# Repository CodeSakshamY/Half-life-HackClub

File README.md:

# Half-life-HackClub
# Psycon-wearable-pcb-V1

custom pcb for my psycon wearable project. designed in easyeda.

## THE BOARD

It is an pcb board loaded with various sensors powered with esp32 as its main brain which would basically help me in making my first version of a smart watch like health wearable
## COMPONENTS

- **ESP32-WROOM-32D** — main microcontroller
- **MAX30102** — optical pulse sensor
- **MPU6050** — accelerometer + gyroscope
- **MCP9808** — temperature sensor
- **ADS1115** — 16-bit adc
- **CH340C** — usb-to-serial interface
- **TP4056** — lithium-ion battery charger
- **AP2112K-3.3** — 3.3v voltage regulator
- **ME6211C18** — 1.8v voltage regulator
- **USB-C + micro-usb connectors**
- **JST-PH connector** — battery connection
- resistors, capacitors, switches and usb protection components

## PCB DESIGN

schematic, component placement and routing are done in easyeda.

## IMAGES

### 3d view

### pcb routing

### schematic

designing is done. next step is getting the board manufactured, recieving it , adding the code and testing it and seeing if everything works!!

The entire pcb was designed in easyeda but duet to the repo submision checks error i have added the .kicad_pcb file but please refer to only the files in the folder named psycon-wearable.

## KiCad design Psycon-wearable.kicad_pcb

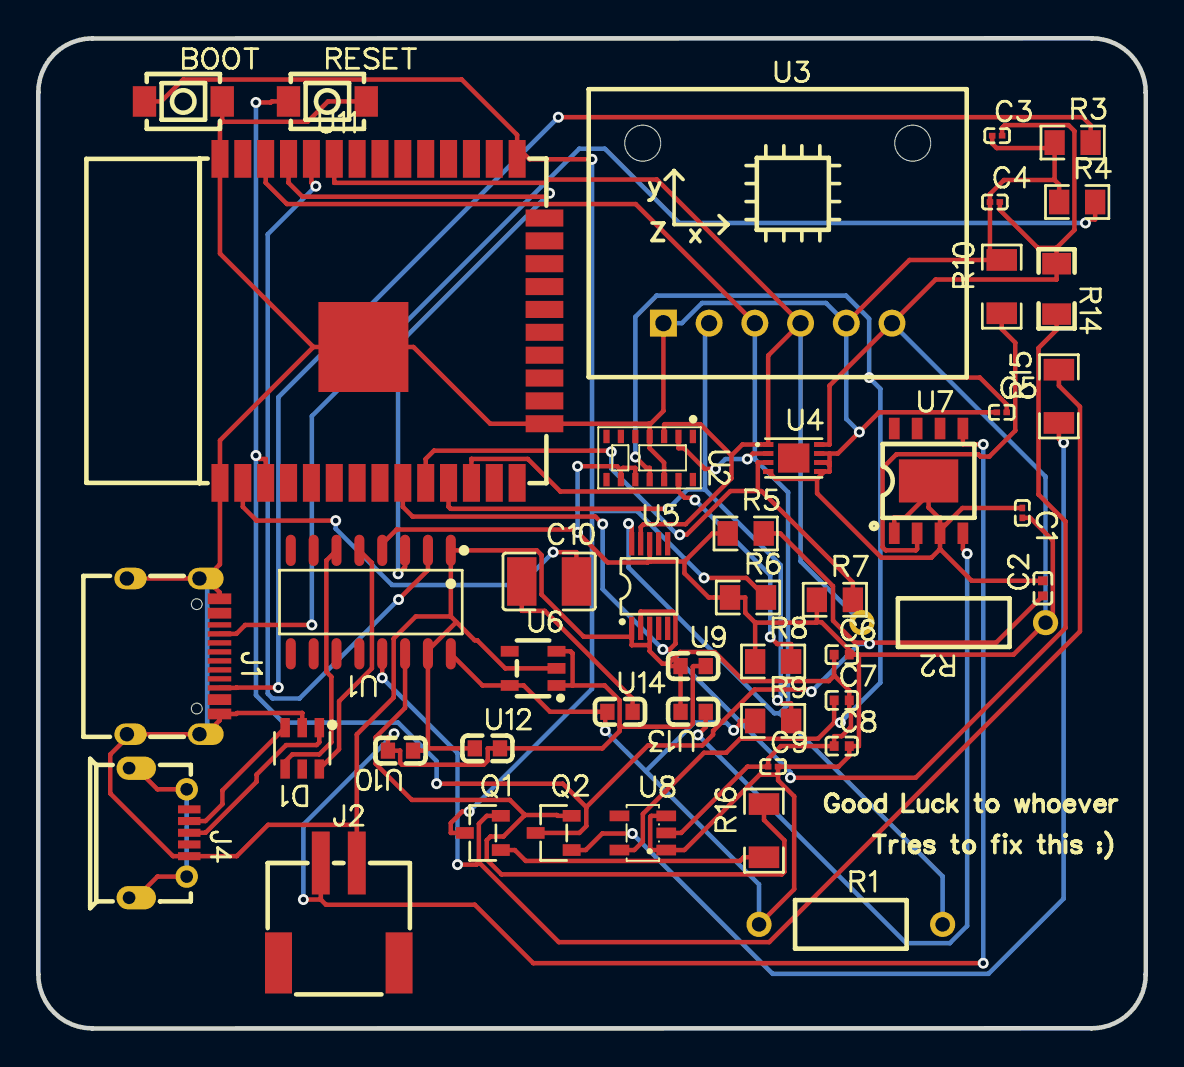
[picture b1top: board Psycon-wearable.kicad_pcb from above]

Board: 2 copper layers, 61.5 x 55.0 mm, 47 parts (0 on the bottom side), 28 nets.

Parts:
C1, C3, C4, C5, C9: 100nF; C0201
C2, C6, C7, C8: 1uF; C0402
C10: 100nF; C1210
D1: MSUSBLC6-2SC6; SOT-23-6_L2.9-W1.6-P0.95-LS2.8-BL
H1, H2: MountingHole; MountingHole_2mm
J1: TYPE-C-31-M-12; USB-C_SMD-TYPE-C-31-M-12_1
J2: JST-PH-2-SMT-RA; CONN-SMD_JST-PH-2-SMT-RA
J4: Micro Usb; MICRO-USB-SMD_MICRO-USB-18
Q1, Q2: AMMBT3904-P2-HF; SOT-23-3_L2.9-W1.3-P1.90-LS2.4-BR
R1, R2: 4.7kΩ; RES-TH_BD2.7-L6.2-P10.20-D0.4
R3, R4: 5.1kΩ; R0805
R5, R6, R7, R8, R9: 10kΩ; R0805
R10: 1.2kΩ; R1206
R14: 10kΩ; R0204
R15, R16: 12kΩ; R1206
SW1, SW2: HX 3X4X2-2P-1.6N TACTILE SWITCH; KEY-SMD_L4.0-W3.0-LS4.9-1
U1: CH340C; SOP-16_L10.0-W3.9-P1.27-LS6.0-BL
U2: MAX30102EFD+T_C6454833; OESIP-14_L5.6-W3.3-P0.80-TL
U3: MPU6050-TH; COMM-TH_MPU6050-TH
U4: MCP9808T-E/MC; DFN-8_L3.0-W2.0-P0.50-TL-EP-1
U5: ADS1115QDGSRQ1; VSSOP-10_L3.0-W3.0-P0.50-LS4.9-BL
U6: AP2112K-3.3TRG1(MS); SOT-23-5_L2.9-W1.6-P0.95-LS2.7-BR
U7: TP4056 (LX); ESOP-8_L4.9-W3.9-P1.27-LS6.0-BL-EP
U8: ME6211C18M5G-N; SOT-23-5_L3.0-W1.7-P0.95-LS2.8-BR
U9, U10: 1uF; C0603
U11: ESP32-WROOM-32D-H4; WIFIM-SMD_ESP32-WROOM-32D
U12, U13, U14: 10uF; C0603

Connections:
+1V8: C5.2, C7.1, U2.11 (VDD), U8.5 (VOUT)
+3V3: C1.2, C3.2, C4.2, C6.2, C8.2, C9.2, R1.1, R2.1, R5.1, R6.1, R7.1, R8.1, R9.1, R14.1, U1.4 (V3), U1.16 (VCC), U2.9 (VLED+), U2.10 (VLED+), U3.6 (3V3), U4.8 (VDD), U5.8 (VDD), U6.5 (VOUT), U8.1 (VIN), U8.3 (CE), U14.1
+5V: U7.4 (VCC), U13.1
ADC_ALERT: R14.2, U5.2 (ALERT/RDY), U11.9 (IO33)
BAT+: J2.1, U6.1 (VIN), U6.3 (EN), U7.5 (BAT), U9.2, U10.2, U12.2
CC1: J1.A5 (CC1), R4.2
CC2: J1.B5 (CC2), R3.2
CH340_DM: D1.4 (I/O2), U1.6 (D-)
CH340_DP: D1.6 (I/O1), U1.5 (D+)
CHG_PROG: R10.1, U7.2 (PROG)
DTR: Q1.2 (E), R15.2, U1.13 (DTR#)
EN: C2.1, Q2.3 (C), R5.2, SW2.1, U11.3 (EN)
ESP_3V3_PIN: C10.2, U11.2 (3V3)
GND: C1.1, C2.2, C3.1, C4.1, C5.1, C6.1, C7.2, C8.1, C9.1, D1.2 (GND), J1.1 (EH), J1.2 (EH), J1.3 (EH), J1.4 (EH), J1.A1B12 (GND), J1.B1A12 (GND), J2.2, J4.5 (GND), R3.1, R4.1, R10.2, SW1.2, SW2.2, U1.1 (GND), U1.15 (R232), U2.4 (PGND), U2.12 (GND), U3.1 (AD0), U3.5 (GND), U4.4 (GND), U4.5 (A2), U4.6 (A1), U4.7 (A0), U5.1 (ADDR), U5.3 (GND), U6.2 (GND), U7.1 (TEMP), U7.3 (GND), U7.9 (EP), U8.2 (VSS), U9.1, U10.1, U11.1 (GND), U11.15 (GND), U11.38 (GND), U11.39 (GND), U12.1, U13.2
IMU_INT: R9.2, U3.2 (INT), U11.11 (IO26)
IO0: Q1.3 (C), R6.2, SW1.1, U11.25 (IO0)
MAX_INT: R8.2, U2.13 (INT#), U11.12 (IO27)
unnamed: C10.1, U14.2
unnamed: Q1.1 (B), R16.1
unnamed: Q2.1 (B), R15.1
RTS: Q2.2 (E), R16.2, U1.14 (RTS#)
RXD0: U1.2 (TXD), U11.34 (RXD0)
SCL: R1.2, U2.2 (SCL), U3.3 (SCL), U4.2 (SCL), U5.10 (SCL), U11.36 (IO22)
SDA: R2.2, U2.3 (SDA), U3.4 (SDA), U4.1 (SDA), U5.9 (SDA), U11.33 (IO21)
TEMP_ALERT: R7.2, U4.3 (Alert), U11.10 (IO25)
TXD0: U1.3 (RXD), U11.35 (TXD0)
USB_DM: D1.3 (I/O2), J4.2 (D-)
USB_DP: D1.1 (I/O1), J4.3 (D+)
